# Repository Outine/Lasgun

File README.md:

# Lasgun
IR LED blaster and IR receiver for dogfighting mini quads.

Generate 38KHz pulses using timer on either the arduino or the stm32f042 (soic stm32 chip),
Take this and drive 1 or more mosfets with it, which in turn drive IR LEDs. 

Monitor input on capture pin to trigger 'firing', potential for functionality to be selected based on input pulse length. 

Monitor inputs from IR receiver to see if the other quad is shooting at us.

For potential gamification, add extra led driver footprints so we can implement "shields", maybe footprint for a CAN bus if bored. 

Also add P-FET output to toggle power on/off to external flight board on mini quad. 
When mini quad is "shot down" and loses lives, we will kill power to the flight board and drop out of the air. 

#Libraries used
imciner2 has a good kicad library that adds things like 0.1" pin headers etc.

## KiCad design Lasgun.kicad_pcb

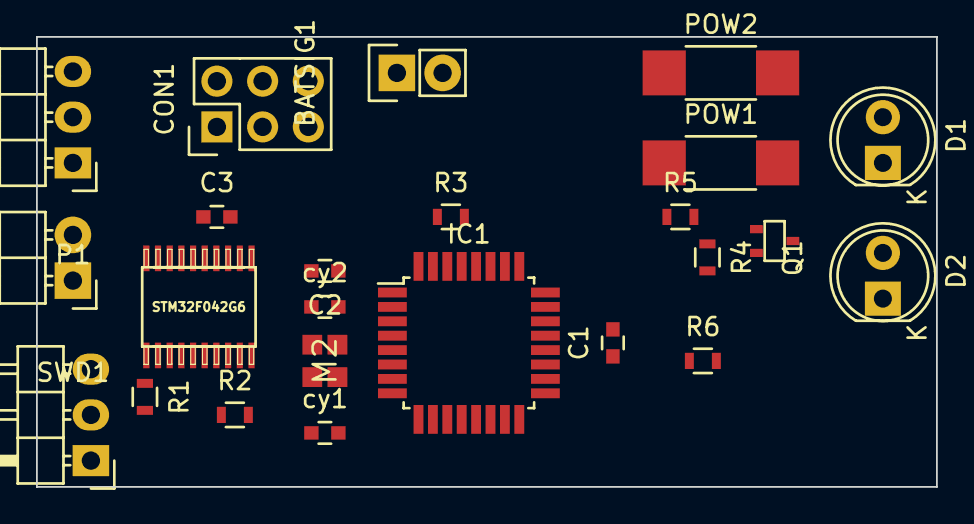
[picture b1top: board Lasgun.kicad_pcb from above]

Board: 2 copper layers, 50.0 x 25.0 mm, 24 parts (0 on the bottom side), 19 nets, no tracks yet.

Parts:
BATSIG1: BAT_SIG; Pin_Header_Straight_1x02
C1, C2, C3: 100nf; C_0603
CON1: AVR-ISP-6; Pin_Header_Straight_2x03
D1, D2: LED; LED-5MM
IC1: ATMEGA328P-A; TQFP-32_7x7mm_Pitch0.8mm
M1: STM32F042G6; James-TSSOP-20
M2: EPSON_FA-20H_CRYSTAL; Ava-EPSON-FA-20H-CRYSTAL
P1, P2: CONN_01X03; Pin_Header_Angled_1x03
POW1, POW2: R; R_2010_HandSoldering
Q1: Q_NMOS_GSD; sc70
R1, R2: 10k; R_0603
R3, R4: 10K; R_0603
R5: 1k; R_0603
R6: 100; R_0603
SWD1: CON_HEADER_1X02-PTH; Pin_Header_Angled_1x02
cy1, cy2: 8pf; C_0603

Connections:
+3V3: BATSIG1.2, C1.1, C2.1, C3.1, CON1.2, IC1.4, IC1.6, IC1.18, IC1.20, M1.5, M1.16, P1.3, P2.3, R3.1
+BATT: POW1.1, POW2.1, R2.2
AVR_PROG_MISO: CON1.1, IC1.16, M1.19
AVR_PROG_MOSI: CON1.4, IC1.15
AVR_PROG_SCK: CON1.3, IC1.17, M1.20
BAT_MON: IC1.19, M1.6, R2.1, R5.2
GND: C1.2, C2.2, C3.2, CON1.6, IC1.3, IC1.5, IC1.21, M1.15, P1.2, P2.2, Q1.2, R1.2, R4.2, R5.1, cy1.2, cy2.2
INPUT_CAPTURE: BATSIG1.1, IC1.12, M1.7
IR_RECEIVER1: IC1.32, P1.1
LED_FET: IC1.13, M1.12, R6.2
MICRO_RXIN: IC1.30, M1.9
MICRO_TXOUT: IC1.31, M1.8
unnamed: D1.1, D2.1, Q1.3
unnamed: D1.2, D2.2, POW1.2, POW2.2
unnamed: IC1.7, M2.3, cy2.1
unnamed: IC1.8, M2.1, cy1.1
unnamed: M1.1, R1.1
unnamed: Q1.1, R4.1, R6.1
~RESET: CON1.5, IC1.29, M1.4, R3.2

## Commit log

2015-11-02 First commit, STM32, AND gate and atmega328
2015-11-02 Added IR receiver, tried to tidy up Kicad libs
2015-11-03 Added datasheets, still working on design
2015-11-04 Refined design, added parts, started to plan board
2015-11-04 Added voltage reg
2015-11-05 routing
